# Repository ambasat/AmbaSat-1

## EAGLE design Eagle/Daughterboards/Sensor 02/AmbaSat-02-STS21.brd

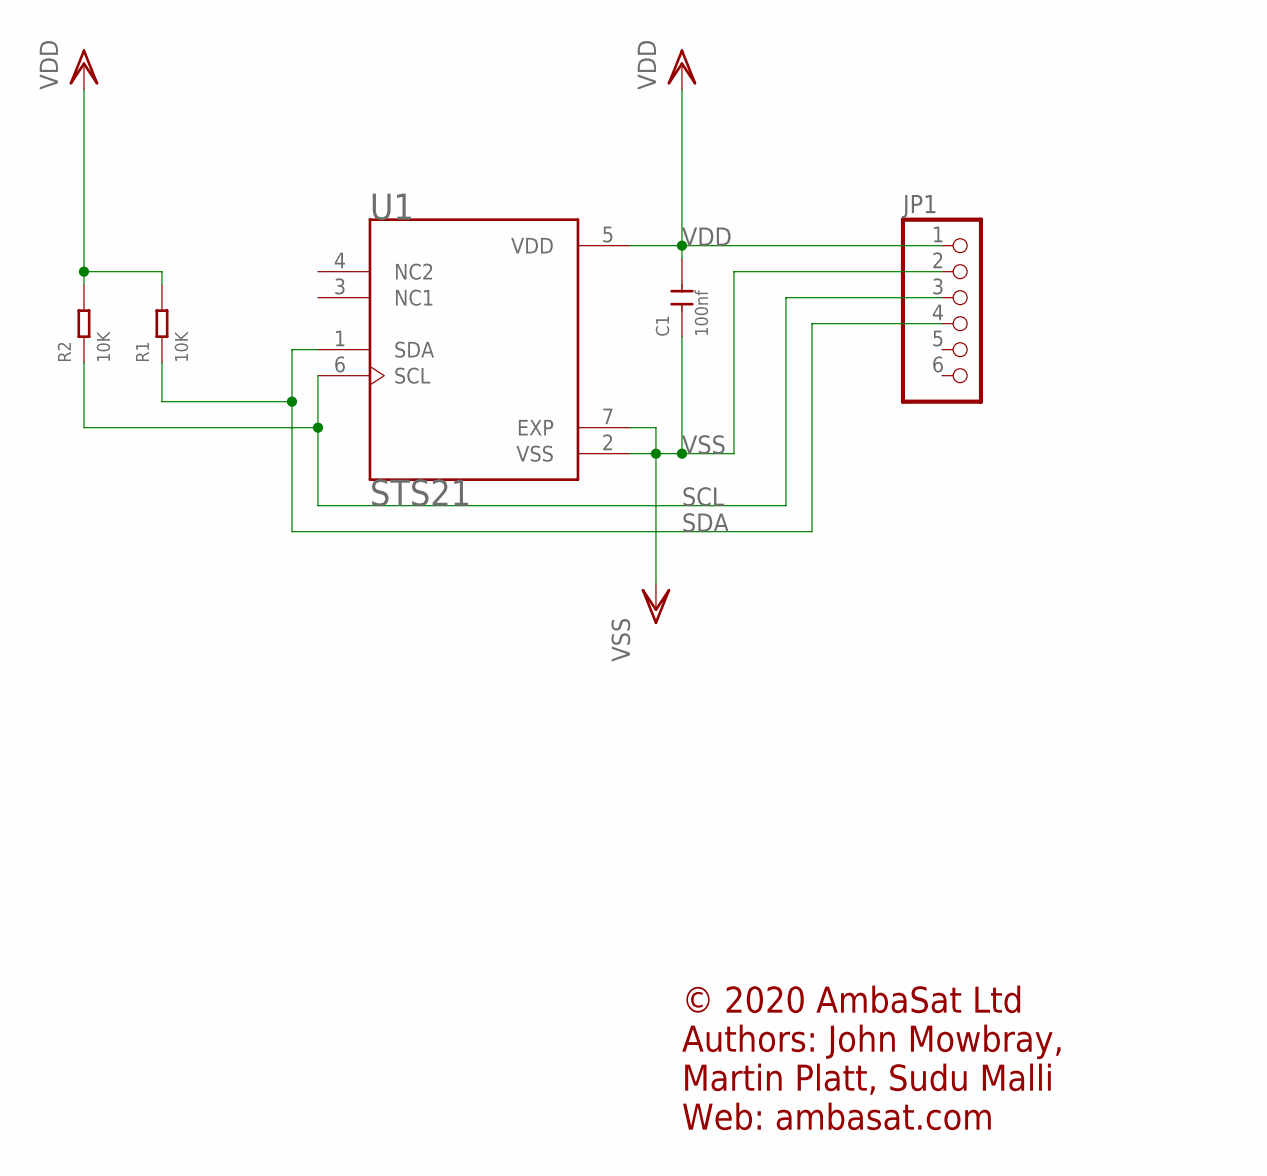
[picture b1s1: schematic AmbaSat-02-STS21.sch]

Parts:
C1: 100nf; C0805
JP1: HEADER-1X6; 1X06_OVAL
R1, R2: 10K; R0805
U1: STS21; XDCR_SGP30-2.5K

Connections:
SCL: JP1.3, R2.1, U1.6 (SCL)
SDA: JP1.4, R1.1, U1.1 (SDA)
VDD: C1.2, JP1.1, R1.2, R2.2, U1.5 (VDD)
VSS: C1.1, JP1.2, U1.2 (VSS), U1.7 (EXP)

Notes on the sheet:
© 2020 AmbaSat Ltd Authors: John Mowbray, Martin Platt, Sudu Malli Web: ambasat.com

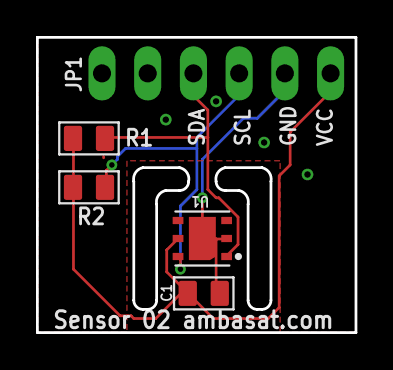
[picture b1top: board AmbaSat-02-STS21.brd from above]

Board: 2 copper layers, 17.7 x 16.4 mm, 5 parts (0 on the bottom side), 4 nets.

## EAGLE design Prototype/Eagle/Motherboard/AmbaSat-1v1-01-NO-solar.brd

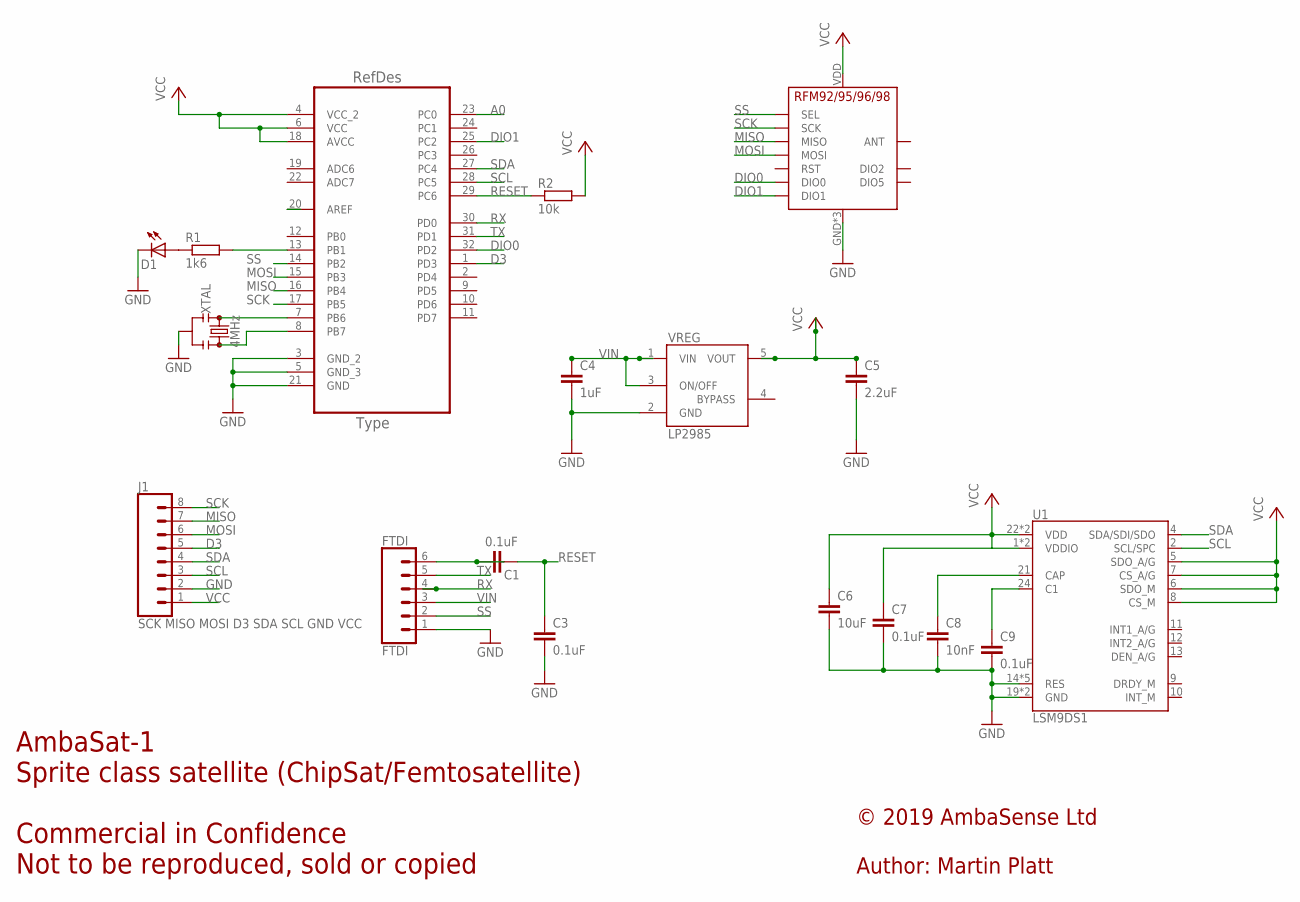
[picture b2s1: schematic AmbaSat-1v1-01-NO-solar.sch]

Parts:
ATMEGA328P-AU: ATMEGA328P-AU; QFP80P900X900X120-32N
C1, C3, C7, C9: 0.1uF; C0805K
C4: 1uF; C0805K
C5: 2.2uF; C0805K
C6: 10uF; C0805K
C8: 10nF; C0805K
D1: LEDCHIP-LED0805; CHIP-LED0805
FTDI: FTDI; 1X06_LONGPADS
J1: SCK MISO MOSI D3 SDA SCL GND VCC; 1X08_LONGPADS
R1: 1k6; M0805
R2: 10k; M0805
RFM95: RFM95
U1: LSM9DS1; LGA24-8X4
VREG: LP2985AIM5-3.3; SOT25
XTAL: 4MHz; RESONATOR-SMD-4.5X2.0

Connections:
A0: ATMEGA328P-AU.23 (PC0)
AREF: ATMEGA328P-AU.20 (AREF)
D3: ATMEGA328P-AU.1 (PD3), J1.5
DIO0: ATMEGA328P-AU.32 (PD2), RFM95.DIO0
DIO1: ATMEGA328P-AU.25 (PC2), RFM95.DIO1
GND: ATMEGA328P-AU.3 (GND_2), ATMEGA328P-AU.5 (GND_3), ATMEGA328P-AU.21 (GND), C3.2, C4.2, C5.2, C6.2, C7.2, C8.2, C9.2, D1.C, FTDI.1, J1.2, RFM95.GND, RFM95.GND1 (GND), RFM95.GND2 (GND), U1.14 (RES), U1.15 (RES), U1.16 (RES), U1.17 (RES), U1.18 (RES), U1.19 (GND), U1.20 (GND), VREG.2 (GND), XTAL.2
MISO: ATMEGA328P-AU.16 (PB4), J1.7, RFM95.MISO
MOSI: ATMEGA328P-AU.15 (PB3), J1.6, RFM95.MOSI
unnamed: ATMEGA328P-AU.7 (PB6), XTAL.1
unnamed: ATMEGA328P-AU.8 (PB7), XTAL.3
unnamed: ATMEGA328P-AU.13 (PB1), R1.2
unnamed: D1.A, R1.1
unnamed: C1.2, FTDI.6
unnamed: C9.1, U1.24 (C1)
unnamed: C8.1, U1.21 (CAP)
RESET: ATMEGA328P-AU.29 (PC6), C1.1, C3.1, R2.1
RX: ATMEGA328P-AU.30 (PD0), FTDI.4
SCK: ATMEGA328P-AU.17 (PB5), J1.8, RFM95.SCK
SCL: ATMEGA328P-AU.28 (PC5), J1.3, U1.2 (SCL/SPC)
SDA: ATMEGA328P-AU.27 (PC4), J1.4, U1.4 (SDA/SDI/SDO)
SS: ATMEGA328P-AU.14 (PB2), FTDI.2, RFM95.NSS (SEL)
TX: ATMEGA328P-AU.31 (PD1), FTDI.5
VCC: ATMEGA328P-AU.4 (VCC_2), ATMEGA328P-AU.6 (VCC), ATMEGA328P-AU.18 (AVCC), C5.1, C6.1, C7.1, J1.1, R2.2, RFM95.VDD (VCC), U1.1 (VDDIO), U1.3 (VDDIO), U1.5 (SDO_A/G), U1.6 (SDO_M), U1.7 (CS_A/G), U1.8 (CS_M), U1.22 (VDD), U1.23 (VDD), VREG.5 (VOUT)
VIN: C4.1, FTDI.3, VREG.1 (VIN), VREG.3 (ON/OFF)

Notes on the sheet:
AmbaSat-1 Sprite class satellite (ChipSat/Femtosatellite) Commercial in Confidence Not to be reproduced, sold or copied
© 2019 AmbaSense Ltd Author: Martin Platt

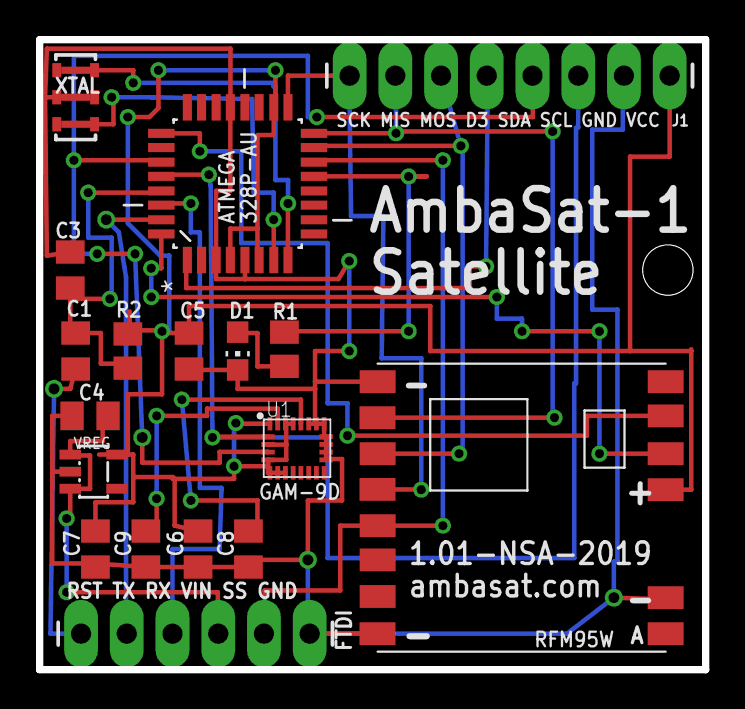
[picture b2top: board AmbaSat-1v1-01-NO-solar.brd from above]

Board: 2 copper layers, 37.0 x 35.0 mm, 18 parts (0 on the bottom side), 22 nets.

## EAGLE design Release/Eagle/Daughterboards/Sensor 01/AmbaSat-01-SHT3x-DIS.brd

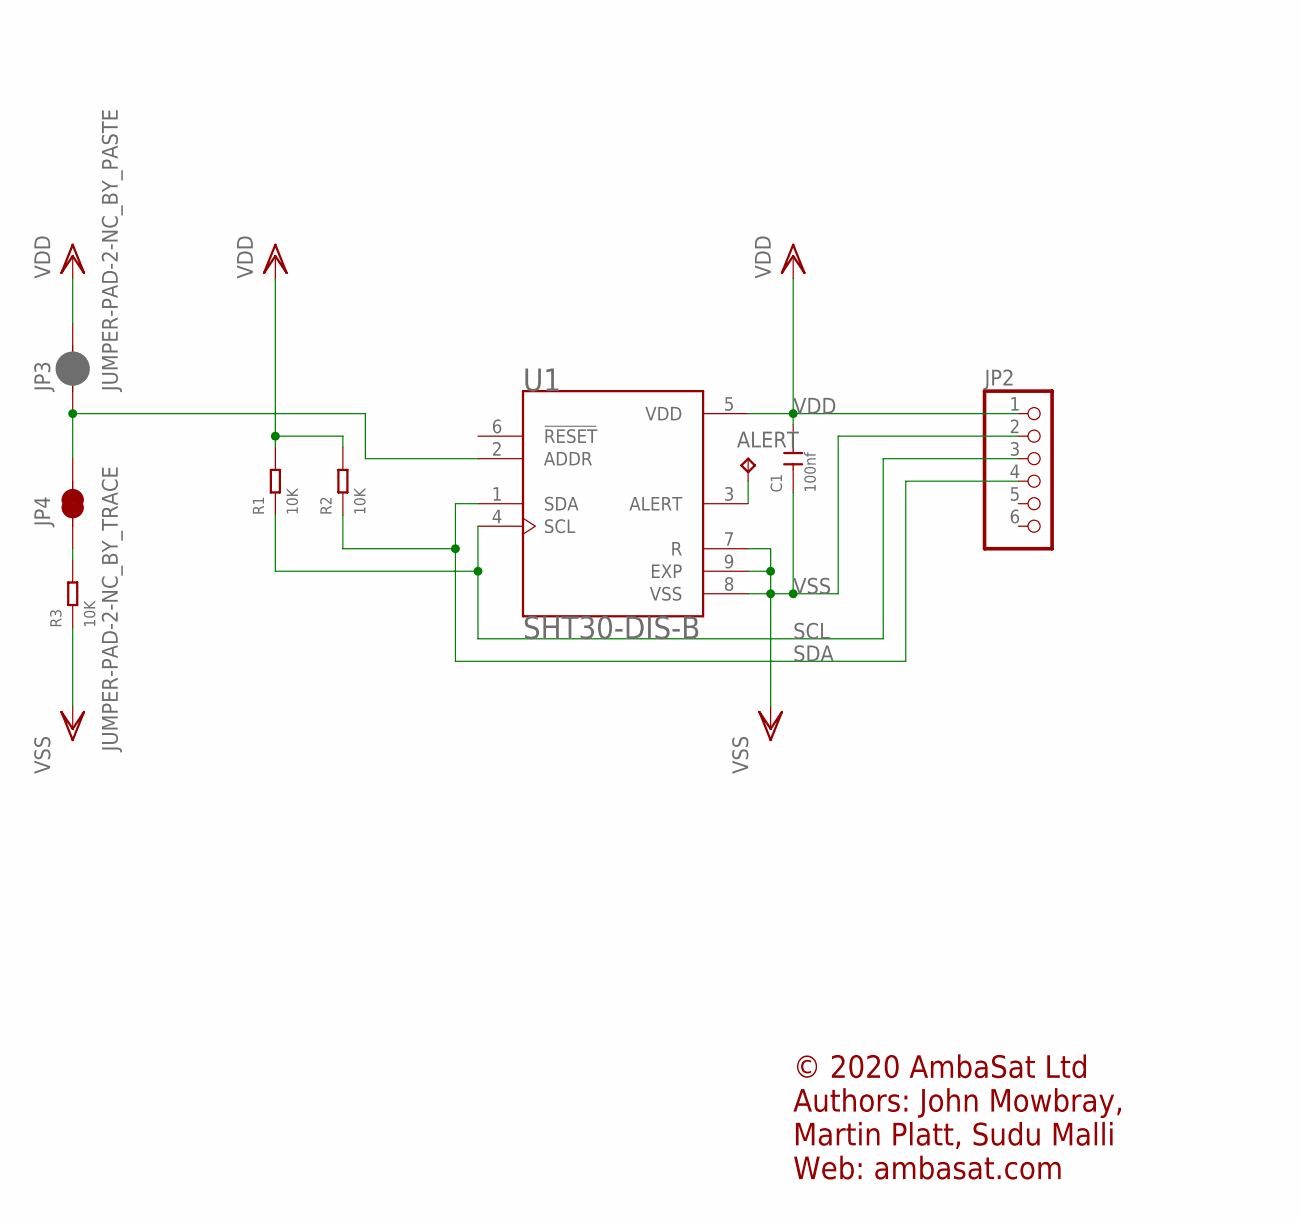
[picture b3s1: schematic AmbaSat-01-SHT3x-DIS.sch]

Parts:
ALERT: TPTP06R; TP06R
C1: 100nf; C0603
JP2: HEADER-1X6; 1X06_OVAL
JP3: JUMPER-PAD-2-NC_BY_PASTE; PAD-JUMPER-2-NC_BY_PASTE_YES_SILK
JP4: JUMPER-PAD-2-NC_BY_TRACE; PAD-JUMPER-2-NC_BY_TRACE_YES_SILK
R1, R2, R3: 10K; R0603
U1: SHT30-DIS-B; DFN250X250X100-9N

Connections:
unnamed: JP3.1, JP4.2, U1.2 (ADDR)
unnamed: ALERT.TP, U1.3 (ALERT)
unnamed: JP4.1, R3.2
SCL: JP2.3, R1.1, U1.4 (SCL)
SDA: JP2.4, R2.1, U1.1 (SDA)
VDD: C1.2, JP2.1, JP3.2, R1.2, R2.2, U1.5 (VDD)
VSS: C1.1, JP2.2, R3.1, U1.7 (R), U1.8 (VSS), U1.9 (EXP)

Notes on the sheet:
© 2020 AmbaSat Ltd Authors: John Mowbray, Martin Platt, Sudu Malli Web: ambasat.com

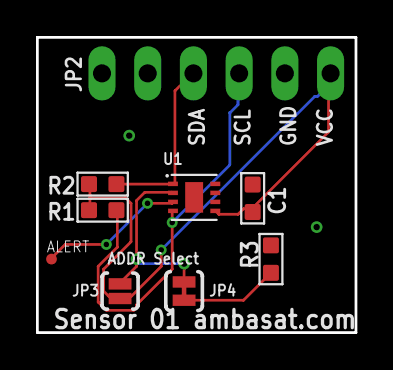
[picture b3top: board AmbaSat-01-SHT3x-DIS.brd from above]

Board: 2 copper layers, 17.7 x 16.4 mm, 9 parts (0 on the bottom side), 7 nets.

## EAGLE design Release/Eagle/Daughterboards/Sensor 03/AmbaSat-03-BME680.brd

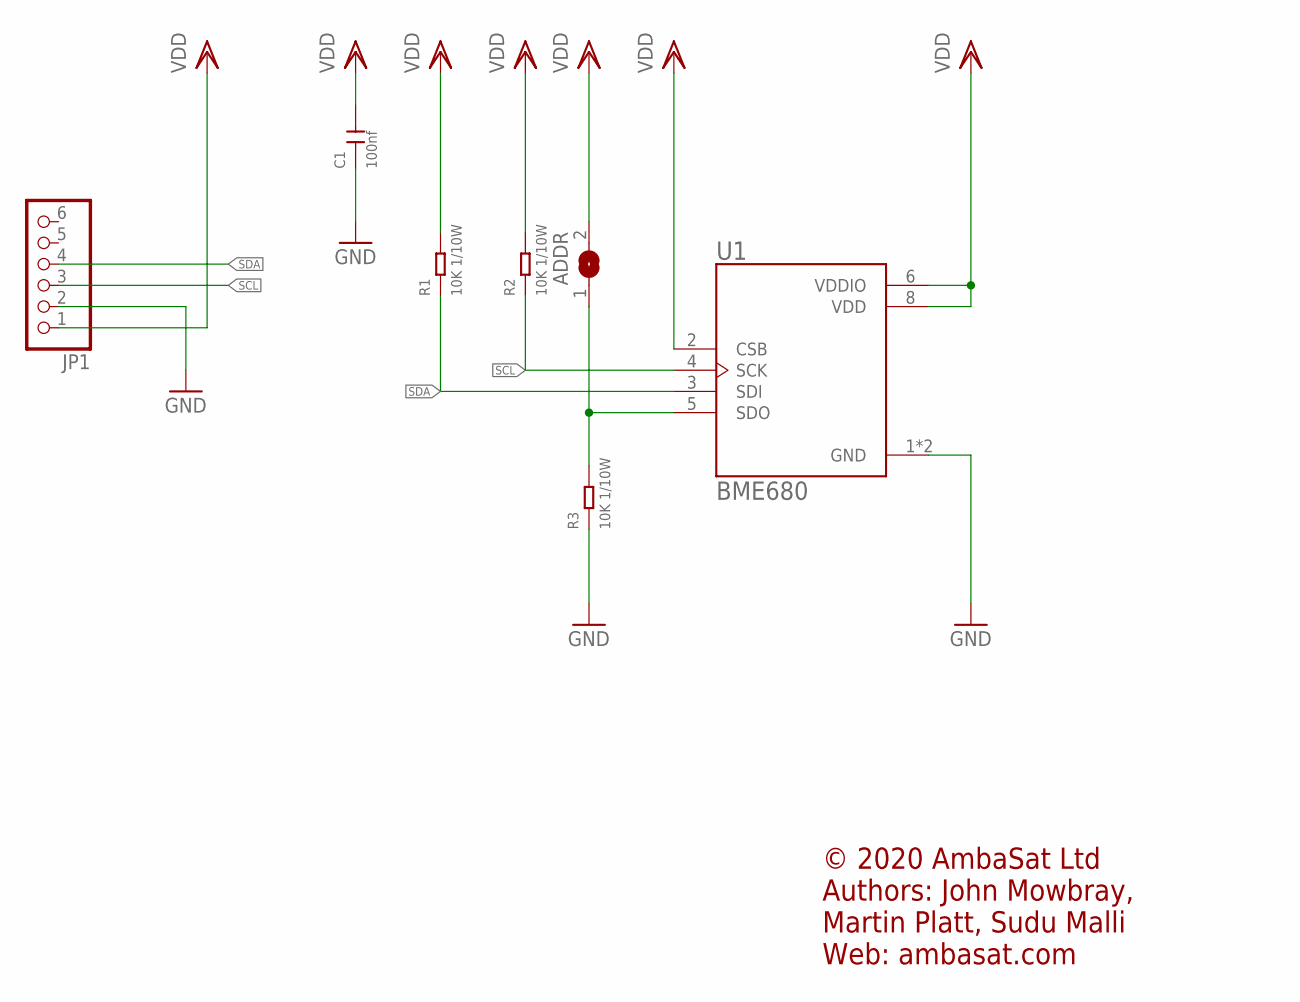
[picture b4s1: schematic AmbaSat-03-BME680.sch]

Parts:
ADDR: SJ
C1: 100nf; C0603
JP1: HEADER-1X6; 1X06_OVAL
R1, R2, R3: 10K 1/10W; R0603
U1: BME680; PSON80P300X300X100-8N

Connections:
GND: C1.1, JP1.2, R3.1, U1.1 (GND), U1.7 (GND)
unnamed: ADDR.1, R3.2, U1.5 (SDO)
SCL: JP1.3, R2.1, U1.4 (SCK)
SDA: JP1.4, R1.1, U1.3 (SDI)
VDD: ADDR.2, C1.2, JP1.1, R1.2, R2.2, U1.2 (CSB), U1.6 (VDDIO), U1.8 (VDD)

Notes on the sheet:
© 2020 AmbaSat Ltd Authors: John Mowbray, Martin Platt, Sudu Malli Web: ambasat.com

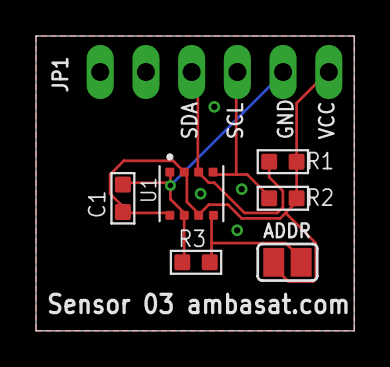
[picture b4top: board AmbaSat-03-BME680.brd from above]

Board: 2 copper layers, 17.7 x 16.4 mm, 7 parts (0 on the bottom side), 5 nets.

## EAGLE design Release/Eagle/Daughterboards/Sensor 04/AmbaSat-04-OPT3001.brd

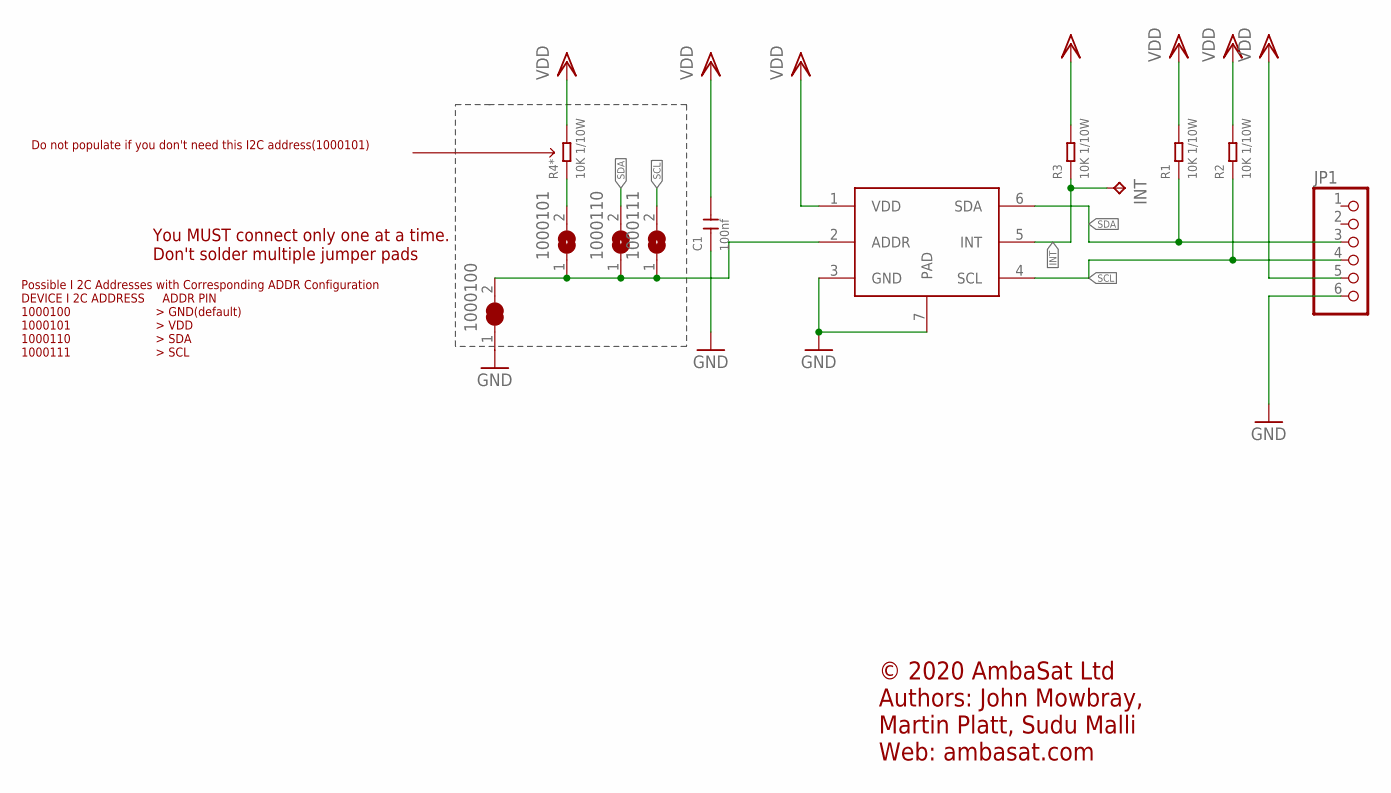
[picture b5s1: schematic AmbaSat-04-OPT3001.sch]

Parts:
1000100: SOLDERJUMPER_CLOSED; SOLDERJUMPER_CLOSEDWIRE
1000101, 1000110, 1000111: SJ
C1: 100nf; C0603
INT: TPTP11R; TP11R
JP1: HEADER-1X6; 1X06_OVAL
R1, R2, R3, R4*: 10K 1/10W; R0603
U2: OPT3001; SON65P200X200X65-7N

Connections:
GND: 1000100.1, C1.1, JP1.6, U2.3 (GND), U2.7 (PAD)
INT: INT.TP, R3.1, U2.5 (INT)
unnamed: 1000101.2, R4*.1
unnamed: 1000100.2, 1000101.1, 1000110.1, 1000111.1, U2.2 (ADDR)
SCL: 1000111.2, JP1.4, R2.1, U2.4 (SCL)
SDA: 1000110.2, JP1.3, R1.1, U2.6 (SDA)
VDD: C1.2, JP1.5, R1.2, R2.2, R3.2, R4*.2, U2.1 (VDD)

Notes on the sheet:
You MUST connect only one at a time. Don't solder multiple jumper pads
Possible I 2C Addresses with Corresponding ADDR Configuration DEVICE I 2C ADDRESS ADDR PIN 1000100 > GND(default) 1000101 > VDD 1000110 > SDA 1000111 > SCL
Do not populate if you don't need this I2C address(1000101)
© 2020 AmbaSat Ltd Authors: John Mowbray, Martin Platt, Sudu Malli Web: ambasat.com

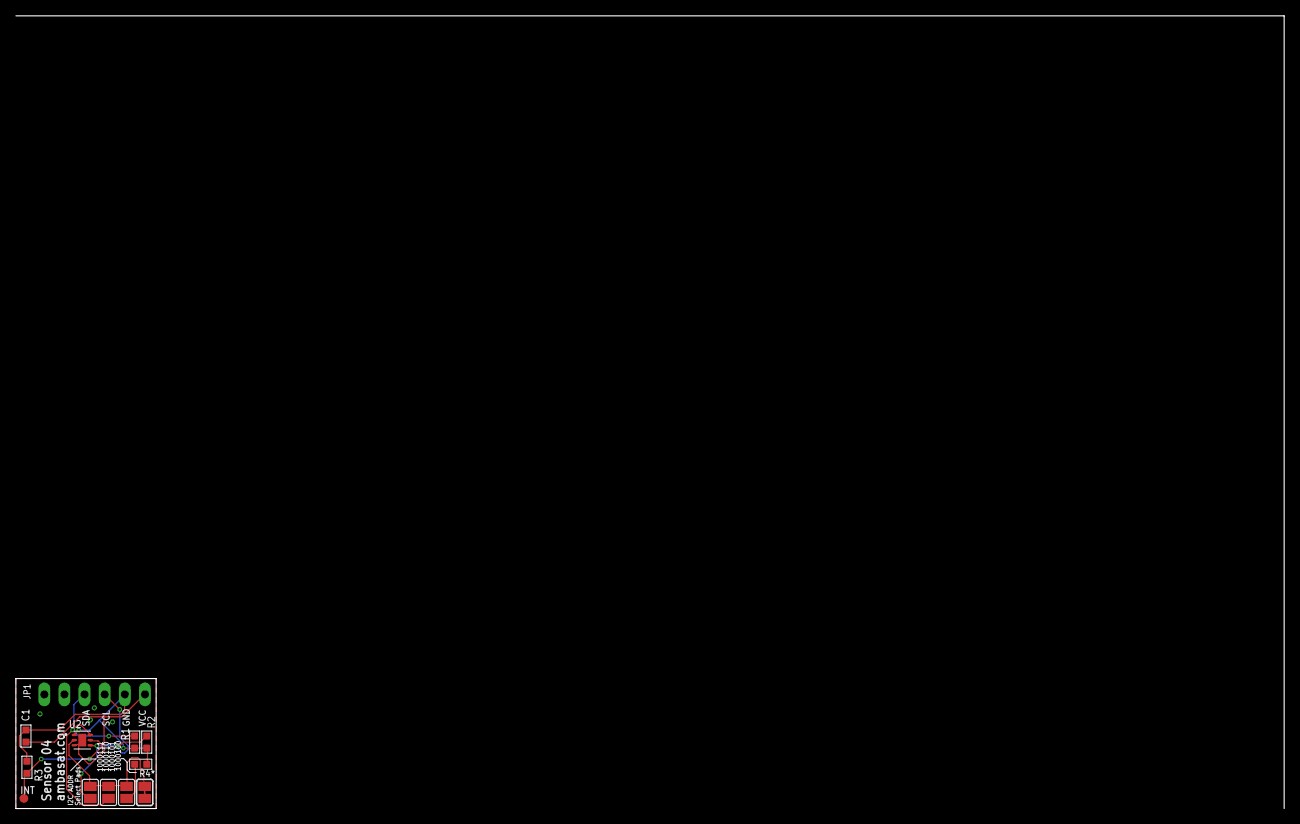
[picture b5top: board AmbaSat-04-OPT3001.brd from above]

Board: 2 copper layers, 17.7 x 16.4 mm, 12 parts (0 on the bottom side), 7 nets.

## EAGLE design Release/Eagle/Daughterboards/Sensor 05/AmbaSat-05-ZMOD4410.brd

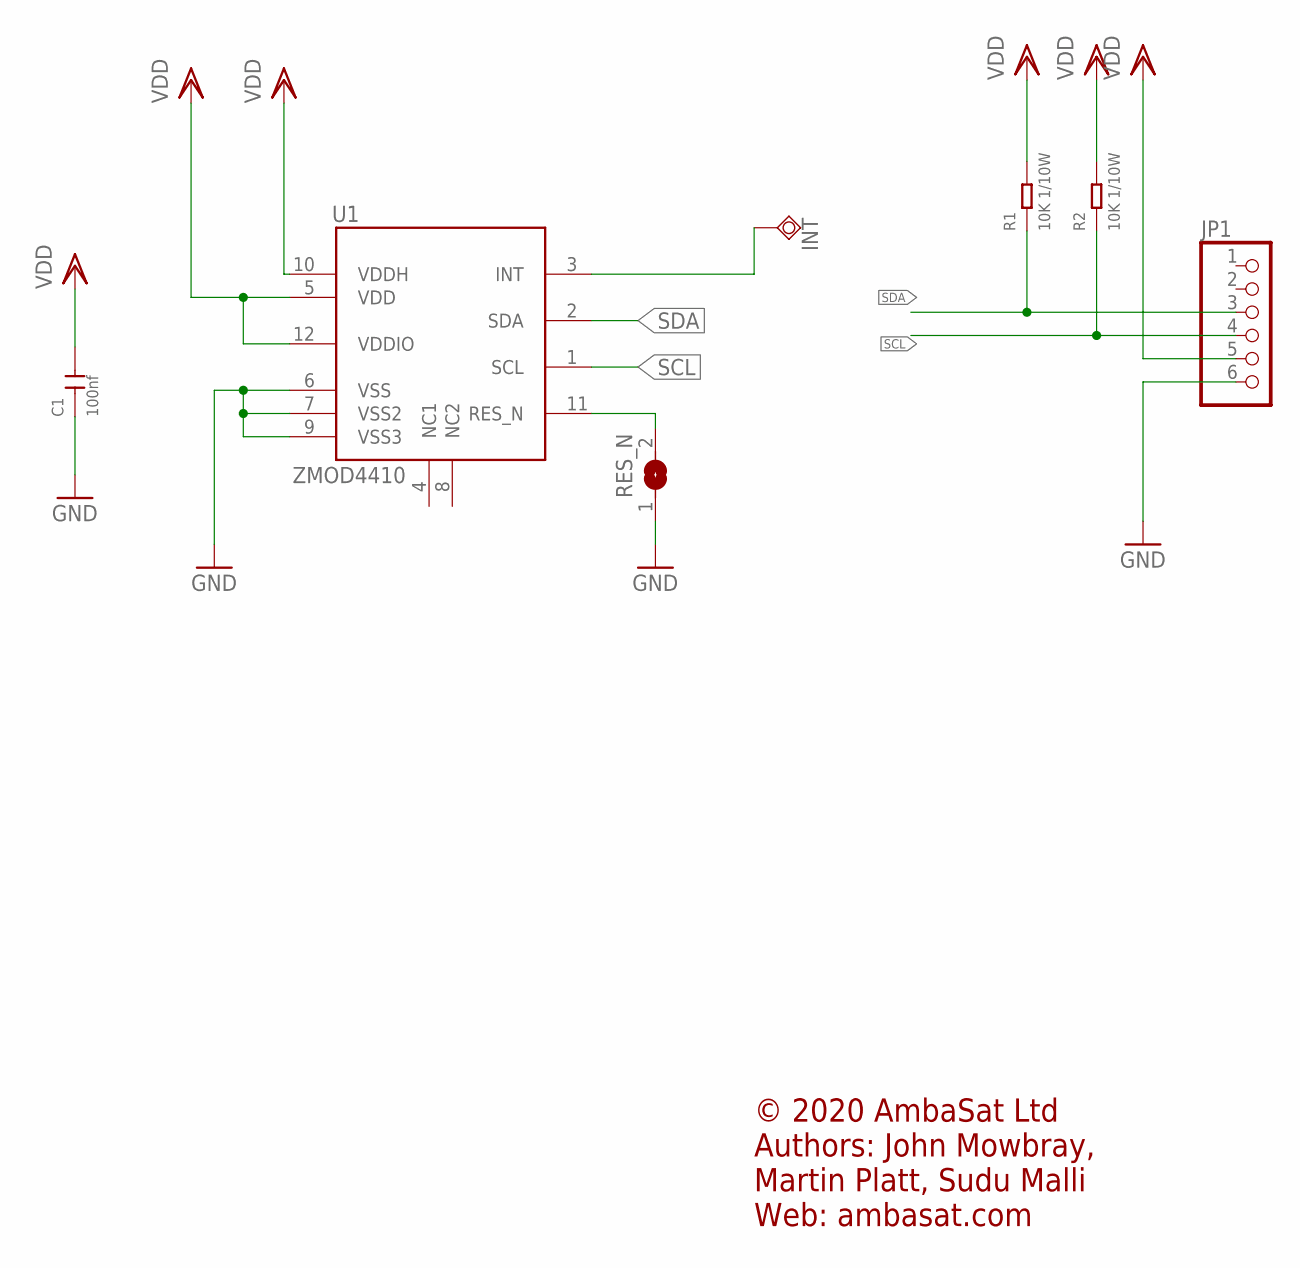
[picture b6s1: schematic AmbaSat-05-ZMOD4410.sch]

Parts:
C1: 100nf; C0603
INT: TESTPAD_TPSQTP12R; TESTPAD_TP12R
JP1: HEADER-1X6; 1X06_OVAL
R1, R2: 10K 1/10W; R0603
RES_N: SJ
U1: ZMOD4410; LGG12D1_3X3X0.7_0.5X1

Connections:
GND: C1.1, JP1.6, RES_N.1, U1.6 (VSS), U1.7 (VSS2), U1.9 (VSS3)
unnamed: INT.TP, U1.3 (INT)
unnamed: RES_N.2, U1.11 (RES_N)
SCL: JP1.4, R2.1, U1.1 (SCL)
SDA: JP1.3, R1.1, U1.2 (SDA)
VDD: C1.2, JP1.5, R1.2, R2.2, U1.5 (VDD), U1.10 (VDDH), U1.12 (VDDIO)

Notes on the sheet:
© 2020 AmbaSat Ltd Authors: John Mowbray, Martin Platt, Sudu Malli Web: ambasat.com

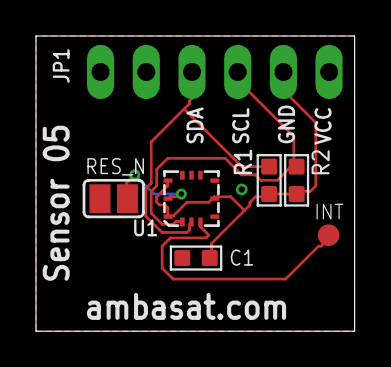
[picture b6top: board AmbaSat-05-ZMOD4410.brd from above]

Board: 2 copper layers, 17.7 x 16.4 mm, 7 parts (0 on the bottom side), 6 nets.

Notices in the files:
parts and their libraries:
microbuilder: This work is placed in the public domain, and may be freely used for commercial and non-commercial work with the following conditions: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
SparkFun-Passives: Licensing: Creative Commons ShareAlike 4.0 International - https://creativecommons.org/licenses/by-sa/4.0
